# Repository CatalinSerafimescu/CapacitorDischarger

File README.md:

# 600V Capacitor Discharger

A professional, handheld capacitor discharger designed for safely discharging high-voltage capacitors in hobby electronics restoration — tube amplifiers, vintage radios, CRT televisions, and consumer power supplies.

---

## Features

- Discharges capacitors up to **600V** in **under 60 seconds** (up to ~1200µF)
- **Adaptive discharge:** controlled current above ~63 V (slow resistive path); fast dump below (MOSFET-switched). Switch point 55–83 V across Q1 hFE (25–300) and 0–60 °C corners; peak fast-dump current ≤ 1.6 A
- **Red LED danger indicator:** ON above ~10V, OFF when safe — powered directly from the capacitor, no external supply. Uses a low-current (2 mA) LED: the chain current is only ~50 µA at 30 V, where a standard LED looks dark
- **Integrated digital voltmeter:** Axiomet PM-128 3½-digit LCD reading volts directly ("600" at 600 V, 1 V steps) via a 10 000:1 divider, powered by any floating external 9 V source plugged into a panel DC jack (5.5×2.1)
- **Reverse polarity protection:** 1N4007 full-bridge rectifier
- **Protection fuse:** 600V-rated 2A fuse on the HV+ line guards against single-fault conditions
- **Thermal cutoff on R_fast:** if the probes touch a *live* supply below the threshold, Q2 stays on and R_fast would dissipate 41–74 W indefinitely (the 2 A fuse never blows) — a one-shot 133 °C thermal fuse clamped to R_fast opens the fast path; the slow path keeps working. **Still: never connect the tool to a powered circuit.**
- Designed for **DIY assembly** with through-hole components
- A residual ~1.2–1.4V remains on the capacitor (two bridge-diode drops) — below the 10V safe threshold

---

## Building it

Step-by-step build, wiring, test, calibration and use: **[instruction.md](instruction.md)**.
Single-sided board files: `KiCAD/fab_1s/`. 3D-printed case: [mechanical/enclosure/](mechanical/enclosure/README.md).

---

## Schematic

---

## Bill of Materials

See **[bom.md](bom.md)** for the full component list with sourced vs. to-buy status.

**Note on DVM power:** the PM-128 draws ~1 mA from a 9 V source on its own DC jack (~500 h from an alkaline 9 V cell on a plug). Its datasheet requires the supply and the measured input to have separate grounds, so the source must float (battery or double-insulated adapter) — it is **not** connected to circuit GND.

**Note on DVM calibration:** set with the PM-128's own trimmer (R4) against a known DC voltage. The meter's >100 MΩ input doesn't load the divider. (The earlier 0–100 V LED module was dropped: its 0.525 MΩ input made the 6:1 divider uncalibratable.)

---

## Reference Designs

This design consolidates ideas from three published reference designs:

| Source | Designer | Reference File |
|--------|----------|----------------|
| [Pieraisa capacitor discharger kit](https://www.pieraisa.it) | Mark Maher/Pieraisa | [pieraisa.md](pieraisa.md) |
| [DIY 600V Capacitor Discharger — Constant Current](https://retronics.no/2024/03/30/diy-600-volts-capacitor-discharger-constant-current/) | Retronics.no | [600V_constant_current.md](600V_constant_current.md) |
| [Capacitor Discharger Deluxe – Smart, Fast & Safe High-Voltage Discharge](https://www.youtube.com/watch?v=5_QUd8iT3_g) | Manuel Caldeira / MAC Electronics | [deluxe.md](deluxe.md) |

---

## Improvements Over Reference Designs

### vs. Pieraisa
- Rated for **600V** (Pieraisa: 500V)
- **Automatic** threshold switching via MOSFET+NPN — no relay, no moving parts, no manual button
- Sharper LED cutoff: **~10.2V** Zener-defined threshold (Pieraisa: ~44V, divider-based)
- LED powered directly from HV+ — independent of relay state
- **Direct-reading voltmeter** with a 10 000:1 divider for the 600V range (Pieraisa's divider is mismatched at ~5:1)
- Each slow-path resistor explicitly stress-derated at 61% of rating at 600V

### vs. Retronics.no (constant current)
- **Faster discharge for large caps:** adaptive resistance allows higher initial current, not capped at 10mA
- Standard **FR4 through-hole PCB** — no aluminium PCB or SMD required
- No exotic ICs (Retronics requires LR8K4-G + 800V CoolMOS MOSFET pre-stage)
- **Integrated voltmeter**, calibratable (not present in Retronics design)
- Defined **10.2V LED cutoff** (Retronics LED is always in the current path — no threshold)

### vs. DeLuxe (Manuel Caldeira)
- MOSFET upgraded to **STP10NK80Z (800V, 0.9 Ω)** — IRF840 (500V) is marginal at 600V
- Slow path split into **5× 4.7kΩ/5W** in series — distributes heat; single 820Ω/10W in DeLuxe is a thermal bottleneck at high voltage with large caps
- **R1 and R5 properly rated** for 600V: 3W, 750V working voltage (DeLuxe leaves ratings unspecified)
- **Zener-defined LED threshold at 10.2V** — DeLuxe LED fades naturally with no defined safe cutoff; note the LED is dim below ~70V, so a low-current (2mA-rated) LED is used
- **Full voltmeter circuit added** with 10 000:1 divider, open-resistor input clamp, and battery-powered LCD meter (not present in DeLuxe)
- Every component carries explicit power and voltage stress analysis in the BOM

---

## Generating the Schematic and BOM

### Schematic

Requires [schemdraw](https://schemdraw.readthedocs.io/):

```
pip install schemdraw
python blocks/gen_full_schematic.py
```

Outputs `blocks/full_schematic.svg`.

### BOM

```
python bom.py
```

This prints a summary to the terminal **and** writes `bom.md` and the shopping list `TO_BUY_list.csv`.

The BOM (`bom.py`) is the single source of truth for all component data. It combines:
- **Design decisions** — part values, ratings, and stress calculations recorded directly in the BOM entries
- **Sourced components** — parts already in hand from the TME order (see [sourced_components.md](sourced_components.md)), marked `sourced` or `sourced_partial`
- **Parts to buy** — marked `buy`, with suggested part numbers

Schematic labels are generated from the same BOM data via the `LABEL` dictionary, so updating a value in `bom.py` automatically flows through to the schematic on the next generation run.

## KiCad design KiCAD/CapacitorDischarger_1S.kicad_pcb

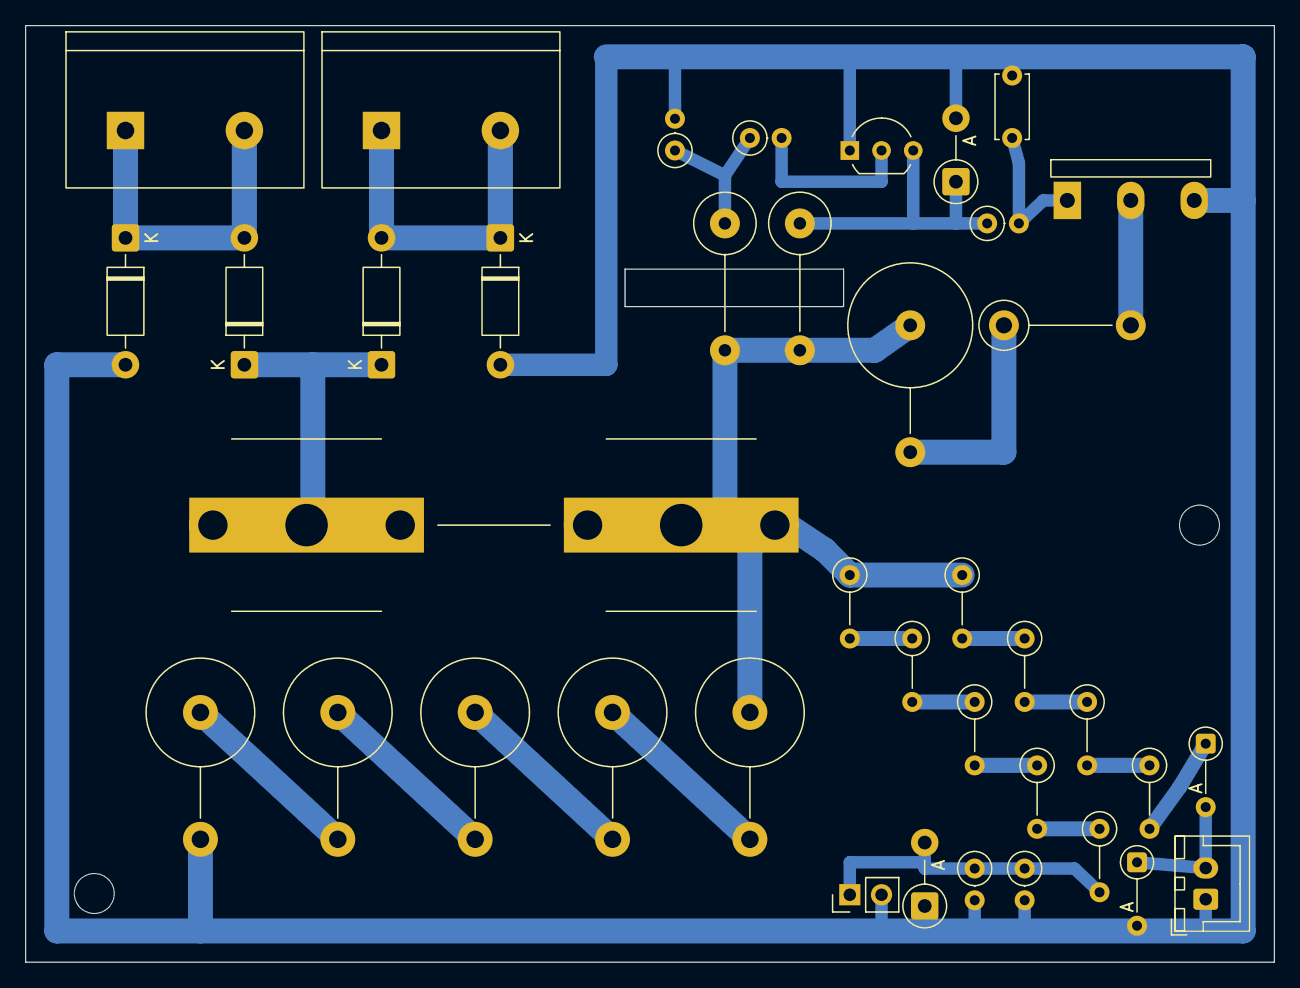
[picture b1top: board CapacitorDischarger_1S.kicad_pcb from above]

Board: 2 copper layers, 100.0 x 75.0 mm, 41 parts (0 on the bottom side), 25 nets.

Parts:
C_byp2: 100nF 50V; C_Disc_D5.0mm_W2.5mm_P5.00mm
D1, D2, D3, D4: 1N4007; D_DO-41_SOD81_P10.16mm_Horizontal
D9: BZX85C12; D_DO-41_SOD81_P5.08mm_Vertical_AnodeUp
D_LED1: BZX55C8V2; D_DO-35_SOD27_P5.08mm_Vertical_AnodeUp
D_clamp1: 1N4007; D_DO-41_SOD81_P5.08mm_Vertical_AnodeUp
D_clamp2: BZX55C8V2; D_DO-35_SOD27_P5.08mm_Vertical_AnodeUp
F1: 2A 1000VDC gR; Fuseholder_Clip-10.3x38mm_Schurter_CSO_0751.0506
H1, H3: M3 (nylon screw); MountingHole_3.2mm_M3
J3, J4: MKDS5/2-9.5; TerminalBlock_Phoenix_MKDS-5-2-9.5_1x02_P9.52mm
J5: PM-128 input; PinHeader_1x02_P2.54mm_Vertical
J6: XH LED cable; JST_XH_B2B-XH-A_1x02_P2.50mm_Vertical
Q1: MPSA42; TO-92_Inline_Wide
Q2: STP10NK80Z; TO-220-3_Vertical_LegsSpread_P5.08mm
R1: 1M 3W; R_Axial_DIN0516_L15.5mm_D5.0mm_P10.16mm_Vertical_BodyOnPad2
R2, R3: 10k; R_Axial_DIN0207_L6.3mm_D2.5mm_P2.54mm_Vertical
R4: 100R; R_Axial_DIN0207_L6.3mm_D2.5mm_P2.54mm_Vertical
R5: 470k 3W; R_Axial_DIN0516_L15.5mm_D5.0mm_P10.16mm_Vertical_BodyOnPad2
R_LED1, R_LED2, R_LED3, R_LED4: 100k 0.6W; R_Axial_DIN0207_L6.3mm_D2.5mm_P5.08mm_Vertical
R_fast1: 50R 7W; R_Axial_Ohmite_27J_7W_Vertical
R_sig1, R_sig2, R_sig3, R_sig4, R_sig5: 100k 0.6W; R_Axial_DIN0207_L6.3mm_D2.5mm_P5.08mm_Vertical
R_sig_bot1, R_sig_bot2: 100R 1%; R_Axial_DIN0207_L6.3mm_D2.5mm_P2.54mm_Vertical
R_slow1, R_slow2, R_slow3, R_slow4, R_slow5: 4k7 5W; R_Axial_Ohmite_45F_5W_Vertical
TF1: SF129R0 133°C; ThermalCutoff_SEFUSE_SF_Vertical

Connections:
/BASE_DIV: R1.2, R2.1, R3.1
/BRIDGE_P: D1.1, D3.1, F1.1
/GATE: C_byp2.1, Q2.1, R4.2
/GATE_TOP: D9.1, Q1.3, R4.1, R5.2
/GND: C_byp2.2, D2.2, D4.2, D9.2, D_clamp1.1, D_clamp2.2, J5.2, J6.1, Q1.1, Q2.3, R2.2, R_sig_bot1.2, R_sig_bot2.2, R_slow5.2
/HVp: F1.2, R1.1, R5.1, R_LED1.1, R_fast1.1, R_sig1.1, R_slow1.1
/LED_A: D_LED1.2, D_clamp2.1, J6.2
/PROBE_A: D1.2, D4.1, J3.1, J3.2
/PROBE_B: D2.1, D3.2, J4.1, J4.2
/SIGOUT: D_clamp1.2, J5.1, R_sig5.2, R_sig_bot1.1, R_sig_bot2.1
unnamed: D_LED1.1, R_LED4.2
unnamed: Q1.2, R3.2
unnamed: Q2.2, TF1.2
unnamed: R_LED1.2, R_LED2.1
unnamed: R_LED2.2, R_LED3.1
unnamed: R_LED3.2, R_LED4.1
unnamed: R_fast1.2, TF1.1
unnamed: R_sig1.2, R_sig2.1
unnamed: R_sig2.2, R_sig3.1
unnamed: R_sig3.2, R_sig4.1
unnamed: R_sig4.2, R_sig5.1
unnamed: R_slow1.2, R_slow2.1
unnamed: R_slow2.2, R_slow3.1
unnamed: R_slow3.2, R_slow4.1
unnamed: R_slow4.2, R_slow5.1

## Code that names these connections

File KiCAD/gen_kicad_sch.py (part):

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W((65, 89), (72, 89))                       # R4 → C_byp2 / gate
W((72, 89), (78, 89))
junctions += [(52, 89), (72, 89)]
labels += [("GATE_TOP", 42, 89, 0), ("GATE", 78, 89, 0), ("BASE_DIV", 15, 95, 0)]
note(8, 110, "Above ~63 V: Q1 saturates → GATE_TOP low → Q2 off (slow path only).\n"
             "Below ~63 V: Q1 off → R5 pulls GATE_TOP up to 12 V (D9) → Q2 on (fast path).\n"
             "R4 + C_byp2: gate filter, keeps Q2 off during hot-plug.")
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W((184, 114), (198, 114))
W((198, 114), (220, 114))
junctions += [(170, 114), (184, 114), (198, 114)]
labels += [("SIGOUT", 162, 114, 0)]
part("DVM1", "DVM", "Axiomet PM-128", "", 244, 115, 0,
     {"1": "SIGOUT", "2": "GND", "3": "BATT_P", "4": "BATT_N"}, on_board=False)
part("BT1", "BAT", "9V ext. via DC jack", "", 266, 115, 0, {"1": "BATT_P", "2": "BATT_N"}, on_board=False)
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
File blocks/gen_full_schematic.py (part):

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    # PROBE_A / PROBE_B terminals
    d.add(elm.Dot().at((0, MID_Y)))
    d.add(elm.Line().left(1.5).at((0, MID_Y)))
    d.add(elm.Dot(open=True).at((-1.5, MID_Y)).label('PROBE_A', loc='left'))

    d.add(elm.Dot().at((4, MID_Y)))
    d.add(elm.Line().right(1.5).at((4, MID_Y)))
    d.add(elm.Dot(open=True).at((5.5, MID_Y)).label('PROBE_B', loc='right'))

    # Top bridge rail: D1 cathode ── D3 cathode
    d.add(elm.Line().right().at((0, HV_Y)).tox(4))
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
    # R4 (100 Ω gate series) from Q2.gate rightward → GATE_CTRL net
    R4e = d.add(elm.Resistor().right().at(q2.gate).length(EL))
    d.add(elm.Label().at(((q2.gate[0] + R4e.end[0]) / 2, q2.gate[1] + 0.4))
          .label(LABEL['R4'], halign='center', valign='bottom'))
    d.add(elm.Dot(open=True).at(R4e.end).label('GATE_CTRL', loc='right'))

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
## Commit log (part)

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2026-05-01 KiCAD processing
